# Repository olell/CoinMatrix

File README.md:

# CoinMatrix

CR2032 sized 8x8 pixel LED matrix driven by a CH32V003. This repo contains
firmware and hardware design files.

## Build the firmware
To build the firmware use the Makefile in the firmware subdirectory. To build
the project you need to clone ch32fun which is included as submodule in this
repo. To do that, run this command:
```
git submodule update --init
```

to build to firmware binary and flash it simply run `make` inside the firmware
directory.

## Hardware
You can find KiCad design files for the current hardware revision in the
hardware/ folder. ⚠️ V2 is currently untested and might have errors!

To view the projects in your browser you can use [KiCanvas](https://github.com/theacodes/kicanvas):
* [matrix board](https://kicanvas.org/?github=https%3A%2F%2Fgithub.com%2Folell%2FCoinMatrix%2Ftree%2Fmain%2Fhardware%2Fcoinmatrix)
* [battery board](https://kicanvas.org/?github=https%3A%2F%2Fgithub.com%2Folell%2FCoinMatrix%2Ftree%2Fmain%2Fhardware%2Fcoinmatrix_battery)
* [spacer](https://kicanvas.org/?github=https%3A%2F%2Fgithub.com%2Folell%2FCoinMatrix%2Ftree%2Fmain%2Fhardware%2Fcoinmatrix_spacer)

### Version 1 Pictures

## License
The hardware is licensed under [CC BY-NC 4.0](https://creativecommons.org/licenses/by-nc/4.0/) you can find a copy of the license text in the LICENSE_HARDWARE file.

The firmware source code is licensed under MIT license, you can find a copy of the license text in the LICENSE file.

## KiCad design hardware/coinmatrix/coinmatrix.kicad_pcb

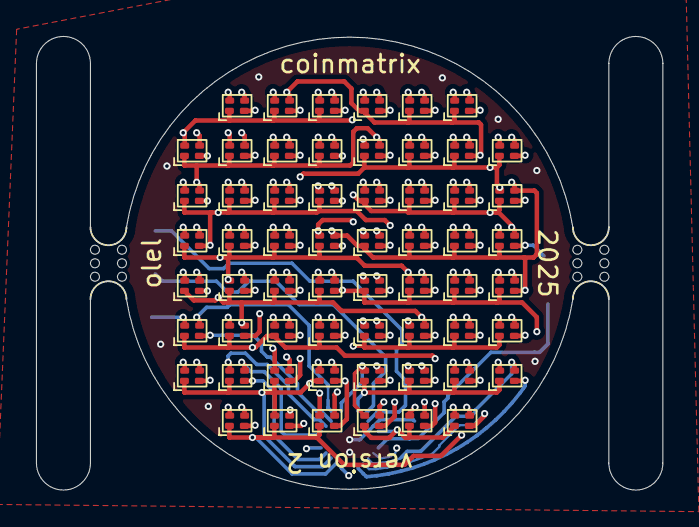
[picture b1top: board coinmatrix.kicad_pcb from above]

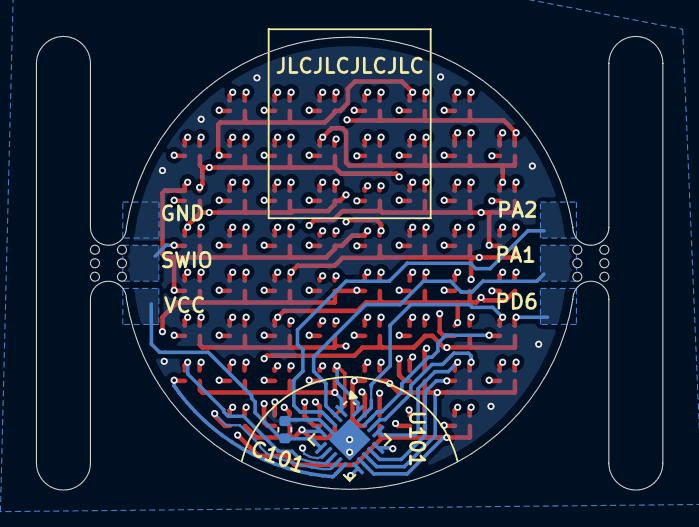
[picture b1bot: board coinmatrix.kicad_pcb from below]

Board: 4 copper layers, 34.8 x 25.2 mm, 64 parts (2 on the bottom side), 18 nets.

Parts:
C101: 100nF; C_0402_1005Metric
D102, D103, D104, D106, D107, D108, D109, D111, D112, D113, D114, D116, D117, D118, D119, D121, D122, D123, D124, D126, D127, D128, D129, D131, D132, D133, D134, D137, D138, D139, D141, D142, D143, D146, D147, D148, D149, D151, D152, D153, D154, D156, D157, D158, D159, D161, D162, D163, D164, D166, D167, D168, D169, D171, D172, D173, D174, D176, D177, D178: LED_RABG; LED-SMD-4P,1.2x1.2mm
U101: CH32V003FxUx; QFN-20-1EP_3x3mm_P0.4mm_EP1.65x1.65mm
mouse-bite-2mm-slot, mouse-bite-2mm-slot#2: VAL**; mouse-bite-2mm-slot

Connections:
/L0: D102.2 (A), D103.2 (A), D104.2 (A), D106.3 (BK), D111.3 (BK), D116.3 (BK), D121.3 (BK), D126.3 (BK), D131.3 (BK), D141.3 (BK), D146.3 (BK), D151.3 (BK), D156.3 (BK), D161.3 (BK), D166.3 (BK), D171.3 (BK), D176.3 (BK), U101.20 (PD6)
/L1: D106.2 (A), D107.2 (A), D108.2 (A), D109.2 (A), D111.4 (GK), D116.4 (GK), D121.4 (GK), D126.4 (GK), D131.4 (GK), D141.4 (GK), D146.4 (GK), D151.4 (GK), D156.4 (GK), D161.4 (GK), D166.4 (GK), D171.4 (GK), D176.4 (GK), U101.19 (PD5)
/L2: D106.4 (GK), D111.2 (A), D112.2 (A), D113.2 (A), D114.2 (A), D116.1 (RK), D121.1 (RK), D126.1 (RK), D131.1 (RK), D141.1 (RK), D146.1 (RK), D151.1 (RK), D156.1 (RK), D161.1 (RK), D166.1 (RK), D171.1 (RK), D176.1 (RK), U101.18 (PD4)
/L3: D106.1 (RK), D111.1 (RK), D116.2 (A), D117.2 (A), D118.2 (A), D119.2 (A), D122.3 (BK), D127.3 (BK), D132.3 (BK), D137.3 (BK), D142.3 (BK), D147.3 (BK), D152.3 (BK), D157.3 (BK), D162.3 (BK), D167.3 (BK), D172.3 (BK), D177.3 (BK), U101.17 (PD3)
/L4: D102.3 (BK), D107.3 (BK), D112.3 (BK), D117.3 (BK), D121.2 (A), D122.2 (A), D123.2 (A), D124.2 (A), D127.4 (GK), D132.4 (GK), D137.4 (GK), D142.4 (GK), D147.4 (GK), D152.4 (GK), D157.4 (GK), D162.4 (GK), D167.4 (GK), D172.4 (GK), D177.4 (GK), U101.16 (PD2)
/L5: D102.4 (GK), D107.4 (GK), D112.4 (GK), D117.4 (GK), D122.4 (GK), D126.2 (A), D127.2 (A), D128.2 (A), D129.2 (A), D132.1 (RK), D137.1 (RK), D142.1 (RK), D147.1 (RK), D152.1 (RK), D157.1 (RK), D162.1 (RK), D167.1 (RK), D172.1 (RK), D177.1 (RK), U101.14 (PC7)
/L6: D102.1 (RK), D107.1 (RK), D112.1 (RK), D117.1 (RK), D122.1 (RK), D127.1 (RK), D131.2 (A), D132.2 (A), D133.2 (A), D134.2 (A), D138.3 (BK), D143.3 (BK), D148.3 (BK), D153.3 (BK), D158.3 (BK), D163.3 (BK), D168.3 (BK), D173.3 (BK), D178.3 (BK), U101.13 (PC6)
/L7: D103.3 (BK), D108.3 (BK), D113.3 (BK), D118.3 (BK), D123.3 (BK), D128.3 (BK), D133.3 (BK), D137.2 (A), D138.2 (A), D139.2 (A), D143.4 (GK), D148.4 (GK), D153.4 (GK), D158.4 (GK), D163.4 (GK), D168.4 (GK), D173.4 (GK), D178.4 (GK), U101.12 (PC5)
/L8: D103.4 (GK), D108.4 (GK), D113.4 (GK), D118.4 (GK), D123.4 (GK), D128.4 (GK), D133.4 (GK), D138.4 (GK), D141.2 (A), D142.2 (A), D143.2 (A), D148.1 (RK), D153.1 (RK), D158.1 (RK), D163.1 (RK), D168.1 (RK), D173.1 (RK), D178.1 (RK), U101.9 (PC2)
/L9: D103.1 (RK), D108.1 (RK), D113.1 (RK), D118.1 (RK), D123.1 (RK), D128.1 (RK), D133.1 (RK), D138.1 (RK), D143.1 (RK), D146.2 (A), D147.2 (A), D148.2 (A), D149.2 (A), D154.3 (BK), D159.3 (BK), D164.3 (BK), D169.3 (BK), D174.3 (BK), U101.7 (PC0)
/L10: D104.3 (BK), D109.3 (BK), D114.3 (BK), D119.3 (BK), D124.3 (BK), D129.3 (BK), D134.3 (BK), D139.3 (BK), D149.3 (BK), D151.2 (A), D152.2 (A), D153.2 (A), D154.2 (A), D159.4 (GK), D164.4 (GK), D169.4 (GK), D174.4 (GK), U101.8 (PC1)
/L11: D104.4 (GK), D109.4 (GK), D114.4 (GK), D119.4 (GK), D124.4 (GK), D129.4 (GK), D134.4 (GK), D139.4 (GK), D149.4 (GK), D154.4 (GK), D156.2 (A), D157.2 (A), D158.2 (A), D159.2 (A), D164.1 (RK), D169.1 (RK), D174.1 (RK), U101.10 (PC3)
/L12: D104.1 (RK), D109.1 (RK), D114.1 (RK), D119.1 (RK), D124.1 (RK), D129.1 (RK), D134.1 (RK), D139.1 (RK), D149.1 (RK), D154.1 (RK), D159.1 (RK), D161.2 (A), D162.2 (A), D163.2 (A), D164.2 (A), U101.15 (PD1)
/L13: D166.2 (A), D167.2 (A), D168.2 (A), D169.2 (A), U101.11 (PC4)
/L14: D171.2 (A), D172.2 (A), D173.2 (A), D174.2 (A), U101.1 (PD7)
/L15: D176.2 (A), D177.2 (A), D178.2 (A), U101.5 (PD0)
GND: C101.1, U101.4 (VSS), U101.21 (VSS)
VCC: C101.2, U101.6 (VDD)

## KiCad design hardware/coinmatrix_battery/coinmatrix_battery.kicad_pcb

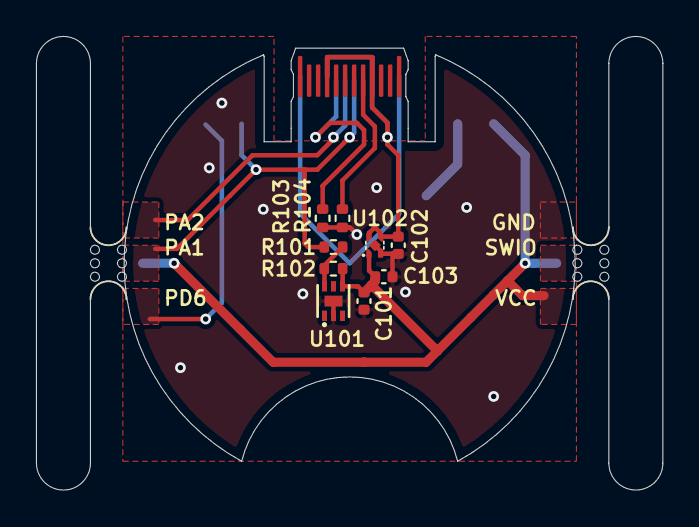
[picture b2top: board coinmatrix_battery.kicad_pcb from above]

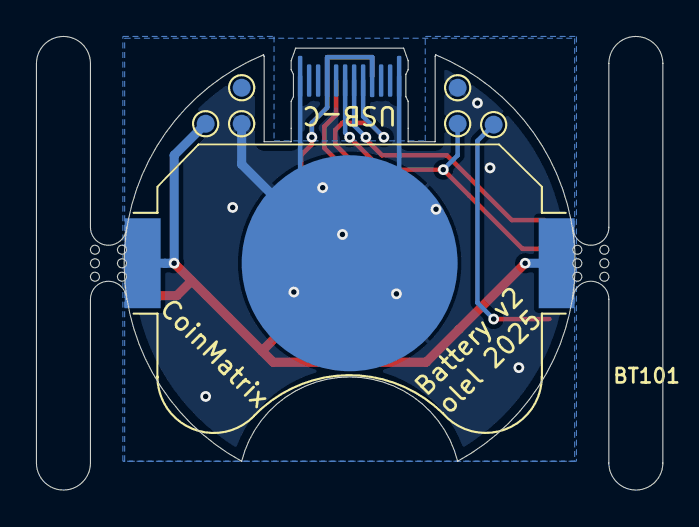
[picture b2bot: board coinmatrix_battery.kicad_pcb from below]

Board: 2 copper layers, 34.8 x 25.2 mm, 19 parts (8 on the bottom side), 7 nets.

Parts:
BT101: Battery_Cell; BatteryHolder_2032
C101: 100nF; C_0402_1005Metric
C102, C103: 1uF; C_0402_1005Metric
P101: USB_C_Plug; USB_C_PADDLE
R101, R103, R104: 5.1kΩ; R_0402_1005Metric
R102: 0; R_0402_1005Metric
TP101, TP102, TP103, TP104, TP105, TP106: TestPoint; TestPoint_Pad_D1.0mm
U101: HAL1255; DFN-6_L1.6-W1.6-P0.50-BL-EP1.0
U102: LW5233; DFN-4_L1.0-W1.0-P0.65-BL-EP
mouse-bite-2mm-slot, mouse-bite-2mm-slot#2: VAL**; mouse-bite-2mm-slot

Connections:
+5V: C102.1, P101.A4 (VBUS), P101.A9 (VBUS), P101.B4 (VBUS), P101.B9 (VBUS), U102.3 (EN), U102.4 (IN)
/DN: P101.A7 (D-), R101.2, TP104.1
/HALL: R101.1, R102.1, U101.6 (OUT)
GND: BT101.2 (-), C101.1, C102.2, C103.2, P101.A1 (GND), P101.A12 (GND), P101.B1 (GND), P101.B12 (GND), R103.2, R104.2, TP103.1, TP105.1, U101.2 (GND), U101.7, U102.2 (GND), U102.5 (EP)
unnamed: P101.A5 (CC), R103.1
unnamed: P101.B5 (VCONN), R104.1
VCC: BT101.1 (+), C101.2, C103.1, R102.2, TP102.1, U101.4 (VDD), U102.1 (OUT)

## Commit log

2025-06-05 Added firmware code
2025-06-06 bump
2025-06-06 Moved matrix pinout to charlie.c
2025-06-06 made out_reg pointer volatile
2025-06-06 changed from 3 value rgb to 32-bit colors
2025-06-06 Added out of bounds check
2025-06-06 moved pixel functions to gfx
2025-06-06 add gitignore
2025-06-06 add hsv function
2025-06-06 created cycle animation
2025-06-13 working version
2025-06-16 dump
2025-06-17 working code for hw v1
2025-06-17 ⚰️ remove unused usb code
2025-06-17 ✨ enabled animation cycling
2025-06-17 🔥 remove ledvm
2025-06-17 ♻️ sync non charlie-driver code with main
2025-06-17 🚑 add ch32fun include for systick counter
2025-06-18 🐛 fix unexpected behavior of charlieDisplay
2025-06-18 🙈 Added kicad to gitignore
2025-06-18 ✨ add v2 hardware design files
2025-06-18 💫 enable droplets animation
2025-06-19 ✨ add gif script and move reset script to subdir
2025-06-19 👷 add build action
2025-06-19 📝 add license, some documentation and pictures
2025-06-20 💫 add game of life animation
